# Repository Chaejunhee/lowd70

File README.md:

# lowd70
lowprofile mechanical keyboard

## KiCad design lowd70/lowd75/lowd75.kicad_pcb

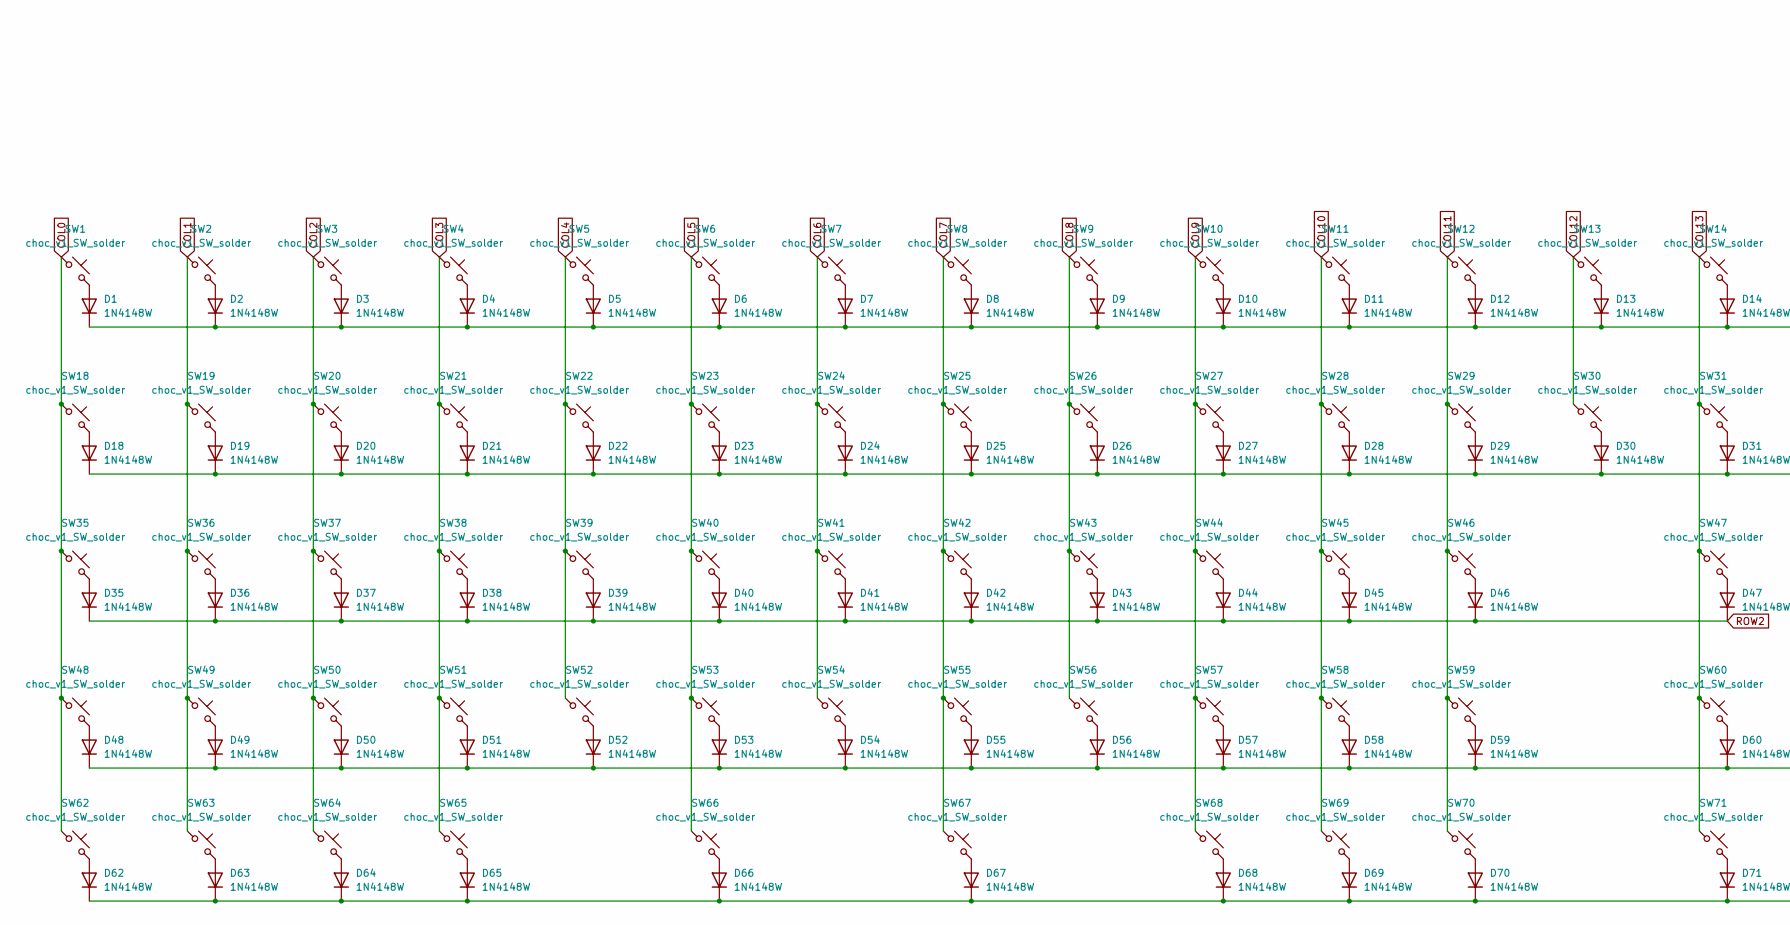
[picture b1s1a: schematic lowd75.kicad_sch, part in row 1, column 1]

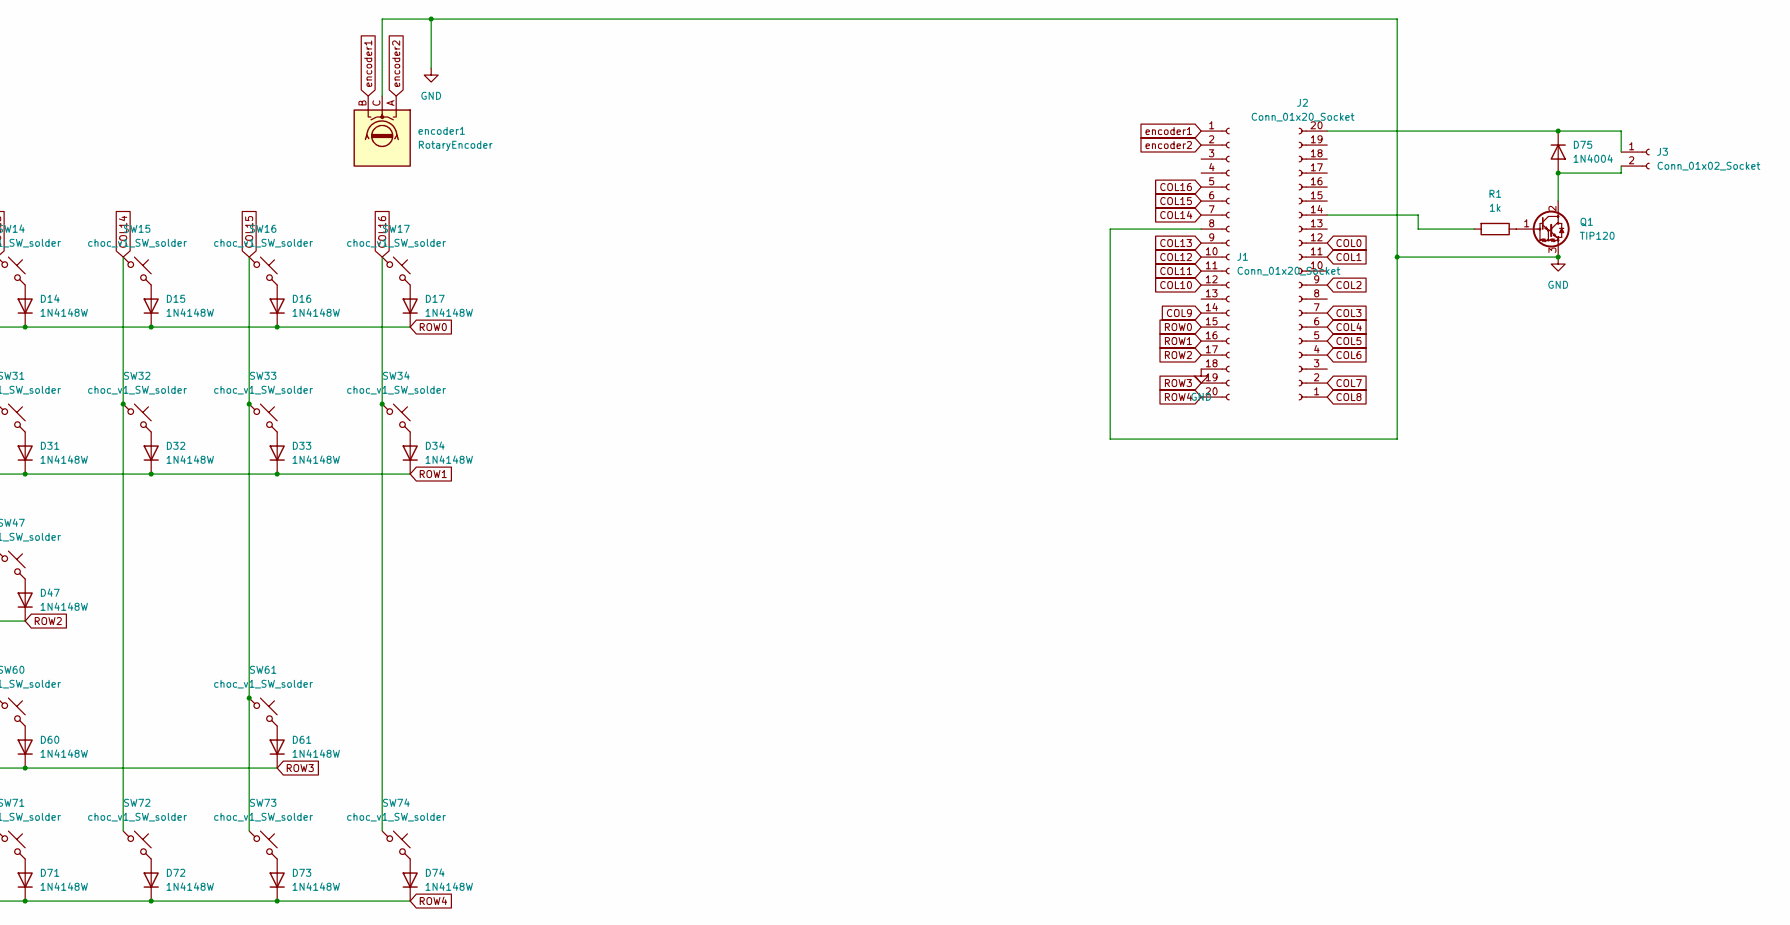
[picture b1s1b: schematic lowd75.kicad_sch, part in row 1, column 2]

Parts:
D1, D2, D3, D4, D5, D6, D7, D8, D9, D10, D11, D12, D13, D14, D15, D16, D17, D18, D19, D20, D21, D22, D23, D24, D25, D26, D27, D28, D29, D30, D31, D32, D33, D34, D35, D36, D37, D38, D39, D40, D41, D42, D43, D44, D45, D46, D47, D48, D49, D50, D51, D52, D53, D54, D55, D56, D57, D58, D59, D60, D61, D62, D63, D64, D65, D66, D67, D68, D69, D70, D71, D72, D73, D74: 1N4148W; D_SOD-123
D75: 1N4004; D_DO-41_SOD81_P10.16mm_Horizontal
J1, J2: Conn_01x20_Socket; PinSocket_1x20_P2.54mm_Vertical
J3: Conn_01x02_Socket; JST_PH_B2B-PH-K_1x02_P2.00mm_Vertical
Q1: TIP120; TO-220-3_Horizontal_TabDown
R1: 1k; R_Axial_DIN0207_L6.3mm_D2.5mm_P7.62mm_Horizontal
SW1, SW2, SW3, SW4, SW5, SW6, SW7, SW8, SW9, SW10, SW11, SW12, SW13, SW14, SW15, SW16, SW17, SW18, SW19, SW20, SW21, SW22, SW23, SW24, SW25, SW26, SW27, SW28, SW29, SW30, SW31, SW32, SW33, SW34, SW35, SW36, SW37, SW38, SW39, SW40, SW41, SW42, SW43, SW44, SW45, SW46, SW47, SW48, SW49, SW50, SW51, SW52, SW53, SW54, SW55, SW56, SW57, SW58, SW59, SW60, SW61, SW62, SW63, SW64, SW65, SW66, SW67, SW68, SW69, SW70, SW71, SW72, SW73, SW74: choc_v1_SW_solder; SW_choc_v1_1u
encoder1: RotaryEncoder; RotaryEncoder_Alps_EC12E_Vertical_H20mm

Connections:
COL0: J2.12, SW1.1, SW18.1, SW35.1, SW48.1, SW62.1
COL1: J2.11, SW2.1, SW19.1, SW36.1, SW49.1, SW63.1
COL2: J2.9, SW3.1, SW20.1, SW37.1, SW50.1, SW64.1
COL3: J2.7, SW4.1, SW21.1, SW38.1, SW51.1, SW65.1
COL4: J2.6, SW5.1, SW22.1, SW39.1, SW52.1
COL5: J2.5, SW6.1, SW23.1, SW40.1, SW53.1, SW66.1
COL6: J2.4, SW7.1, SW24.1, SW41.1, SW54.1
COL7: J2.2, SW8.1, SW25.1, SW42.1, SW55.1, SW67.1
COL8: J2.1, SW9.1, SW26.1, SW43.1, SW56.1
COL9: J1.14, SW10.1, SW27.1, SW44.1, SW57.1, SW68.1
COL10: J1.12, SW11.1, SW28.1, SW45.1, SW58.1, SW69.1
COL11: J1.11, SW12.1, SW29.1, SW46.1, SW59.1, SW70.1
COL12: J1.10, SW13.1, SW30.1
COL13: J1.9, SW14.1, SW31.1, SW47.1, SW60.1, SW71.1
COL14: J1.7, SW15.1, SW32.1, SW72.1
COL15: J1.6, SW16.1, SW33.1, SW61.1, SW73.1
COL16: J1.5, SW17.1, SW34.1, SW74.1
GND: J1.8, J1.18, Q1.3 (E), encoder1.C
unnamed: D1.2 (A), SW1.2
unnamed: D2.2 (A), SW2.2
unnamed: D3.2 (A), SW3.2
unnamed: D4.2 (A), SW4.2
unnamed: D5.2 (A), SW5.2
unnamed: D6.2 (A), SW6.2
unnamed: D7.2 (A), SW7.2
unnamed: D8.2 (A), SW8.2
unnamed: D9.2 (A), SW9.2
unnamed: D10.2 (A), SW10.2
unnamed: D11.2 (A), SW11.2
unnamed: D12.2 (A), SW12.2
unnamed: D13.2 (A), SW13.2
unnamed: D14.2 (A), SW14.2
unnamed: D15.2 (A), SW15.2
unnamed: D16.2 (A), SW16.2
unnamed: D17.2 (A), SW17.2
unnamed: D18.2 (A), SW18.2
unnamed: D19.2 (A), SW19.2
unnamed: D20.2 (A), SW20.2
unnamed: D21.2 (A), SW21.2
unnamed: D22.2 (A), SW22.2
unnamed: D23.2 (A), SW23.2
unnamed: D24.2 (A), SW24.2
unnamed: D25.2 (A), SW25.2
unnamed: D26.2 (A), SW26.2
unnamed: D27.2 (A), SW27.2
unnamed: D28.2 (A), SW28.2
unnamed: D29.2 (A), SW29.2
unnamed: D30.2 (A), SW30.2
unnamed: D31.2 (A), SW31.2
unnamed: D32.2 (A), SW32.2
unnamed: D33.2 (A), SW33.2
unnamed: D34.2 (A), SW34.2
unnamed: D35.2 (A), SW35.2
unnamed: D36.2 (A), SW36.2
unnamed: D37.2 (A), SW37.2
unnamed: D38.2 (A), SW38.2
unnamed: D39.2 (A), SW39.2
unnamed: D40.2 (A), SW40.2
unnamed: D41.2 (A), SW41.2
unnamed: D42.2 (A), SW42.2
unnamed: D43.2 (A), SW43.2
unnamed: D44.2 (A), SW44.2
unnamed: D45.2 (A), SW45.2
unnamed: D46.2 (A), SW46.2
unnamed: D47.2 (A), SW47.2
unnamed: D48.2 (A), SW48.2
unnamed: D49.2 (A), SW49.2
unnamed: D50.2 (A), SW50.2
unnamed: D51.2 (A), SW51.2
unnamed: D52.2 (A), SW52.2
unnamed: D53.2 (A), SW53.2
unnamed: D54.2 (A), SW54.2
unnamed: D55.2 (A), SW55.2
unnamed: D56.2 (A), SW56.2
unnamed: D57.2 (A), SW57.2
unnamed: D58.2 (A), SW58.2
unnamed: D59.2 (A), SW59.2
unnamed: D60.2 (A), SW60.2
unnamed: D61.2 (A), SW61.2
unnamed: D62.2 (A), SW62.2
unnamed: D63.2 (A), SW63.2
unnamed: D64.2 (A), SW64.2
unnamed: D65.2 (A), SW65.2
unnamed: D66.2 (A), SW66.2
unnamed: D67.2 (A), SW67.2
unnamed: D68.2 (A), SW68.2
unnamed: D69.2 (A), SW69.2
unnamed: D70.2 (A), SW70.2
unnamed: D71.2 (A), SW71.2
unnamed: D72.2 (A), SW72.2
unnamed: D73.2 (A), SW73.2
unnamed: D74.2 (A), SW74.2
unnamed: D75.2 (A), J3.2, Q1.2 (C)
unnamed: D75.1 (K), J2.20, J3.1
unnamed: J2.14, R1.2
unnamed: Q1.1 (B), R1.1
ROW0: D1.1 (K), D2.1 (K), D3.1 (K), D4.1 (K), D5.1 (K), D6.1 (K), D7.1 (K), D8.1 (K), D9.1 (K), D10.1 (K), D11.1 (K), D12.1 (K), D13.1 (K), D14.1 (K), D15.1 (K), D16.1 (K), D17.1 (K), J1.15
ROW1: D18.1 (K), D19.1 (K), D20.1 (K), D21.1 (K), D22.1 (K), D23.1 (K), D24.1 (K), D25.1 (K), D26.1 (K), D27.1 (K), D28.1 (K), D29.1 (K), D30.1 (K), D31.1 (K), D32.1 (K), D33.1 (K), D34.1 (K), J1.16
ROW2: D35.1 (K), D36.1 (K), D37.1 (K), D38.1 (K), D39.1 (K), D40.1 (K), D41.1 (K), D42.1 (K), D43.1 (K), D44.1 (K), D45.1 (K), D46.1 (K), D47.1 (K), J1.17
ROW3: D48.1 (K), D49.1 (K), D50.1 (K), D51.1 (K), D52.1 (K), D53.1 (K), D54.1 (K), D55.1 (K), D56.1 (K), D57.1 (K), D58.1 (K), D59.1 (K), D60.1 (K), D61.1 (K), J1.19
ROW4: D62.1 (K), D63.1 (K), D64.1 (K), D65.1 (K), D66.1 (K), D67.1 (K), D68.1 (K), D69.1 (K), D70.1 (K), D71.1 (K), D72.1 (K), D73.1 (K), D74.1 (K), J1.20
encoder1: J1.1, encoder1.B
encoder2: J1.2, encoder1.A

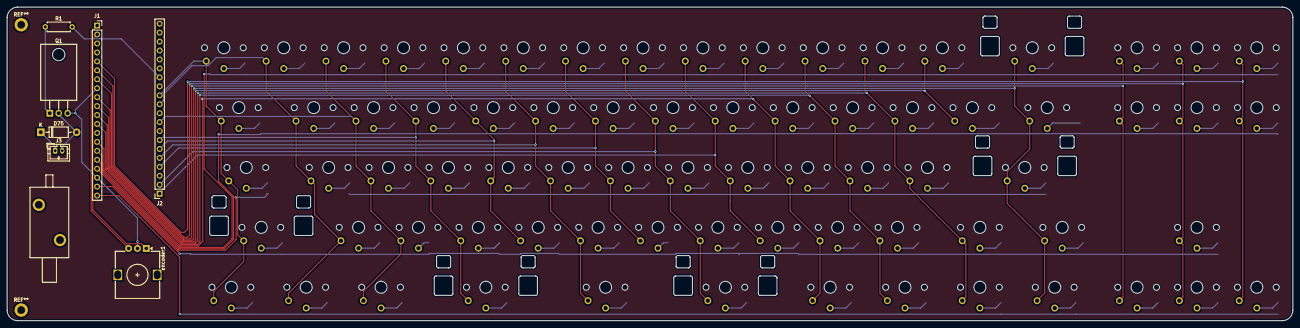
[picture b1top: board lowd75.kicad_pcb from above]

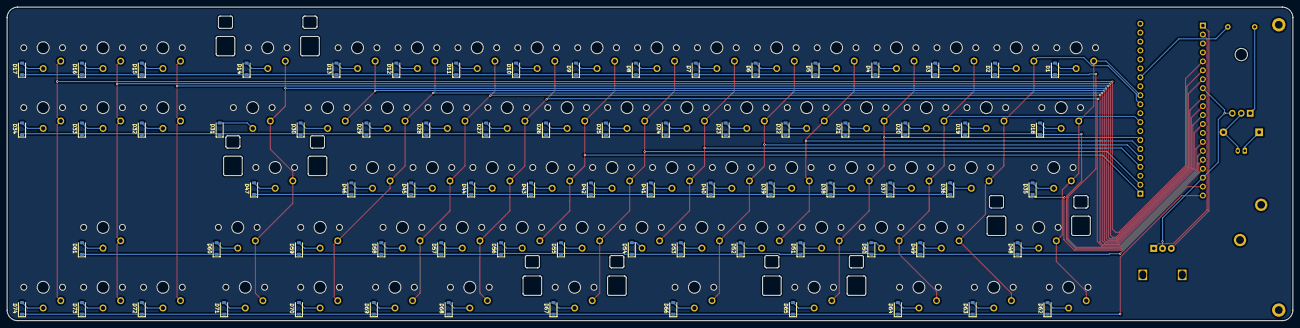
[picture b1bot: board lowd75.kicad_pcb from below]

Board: 2 copper layers, 364.9 x 88.9 mm, 155 parts (74 on the bottom side), 103 nets.

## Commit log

2025-12-10 Add images to README.md
    Added images to README for better visual representation.
